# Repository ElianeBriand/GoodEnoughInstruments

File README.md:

PCB designs &amp; software for DIY instrumentation and random stuffs.

No guarantee whatsoever of fitness for purpose.

# Description of projects

- USB_JTAG: a 3.3v USB-to-JTAG board based on a FTDI chip. Can also be used in USB-to-Serial and other FTDI-supported mode. Finished and working

- Watercooling4cats: Formally a miniature air/floor cooler for my cat (gets hot in the summer). Based on watercooling supplies, a stock CPU fan and a peltier. Can be used as the cooling system for a thermally controlled small enclosure (with temperature feedback) when the cat considers it unnecessary. Hardware is mostly done (a few bodge to be added to the current board file), firmware being written (FreeRTOS-based)

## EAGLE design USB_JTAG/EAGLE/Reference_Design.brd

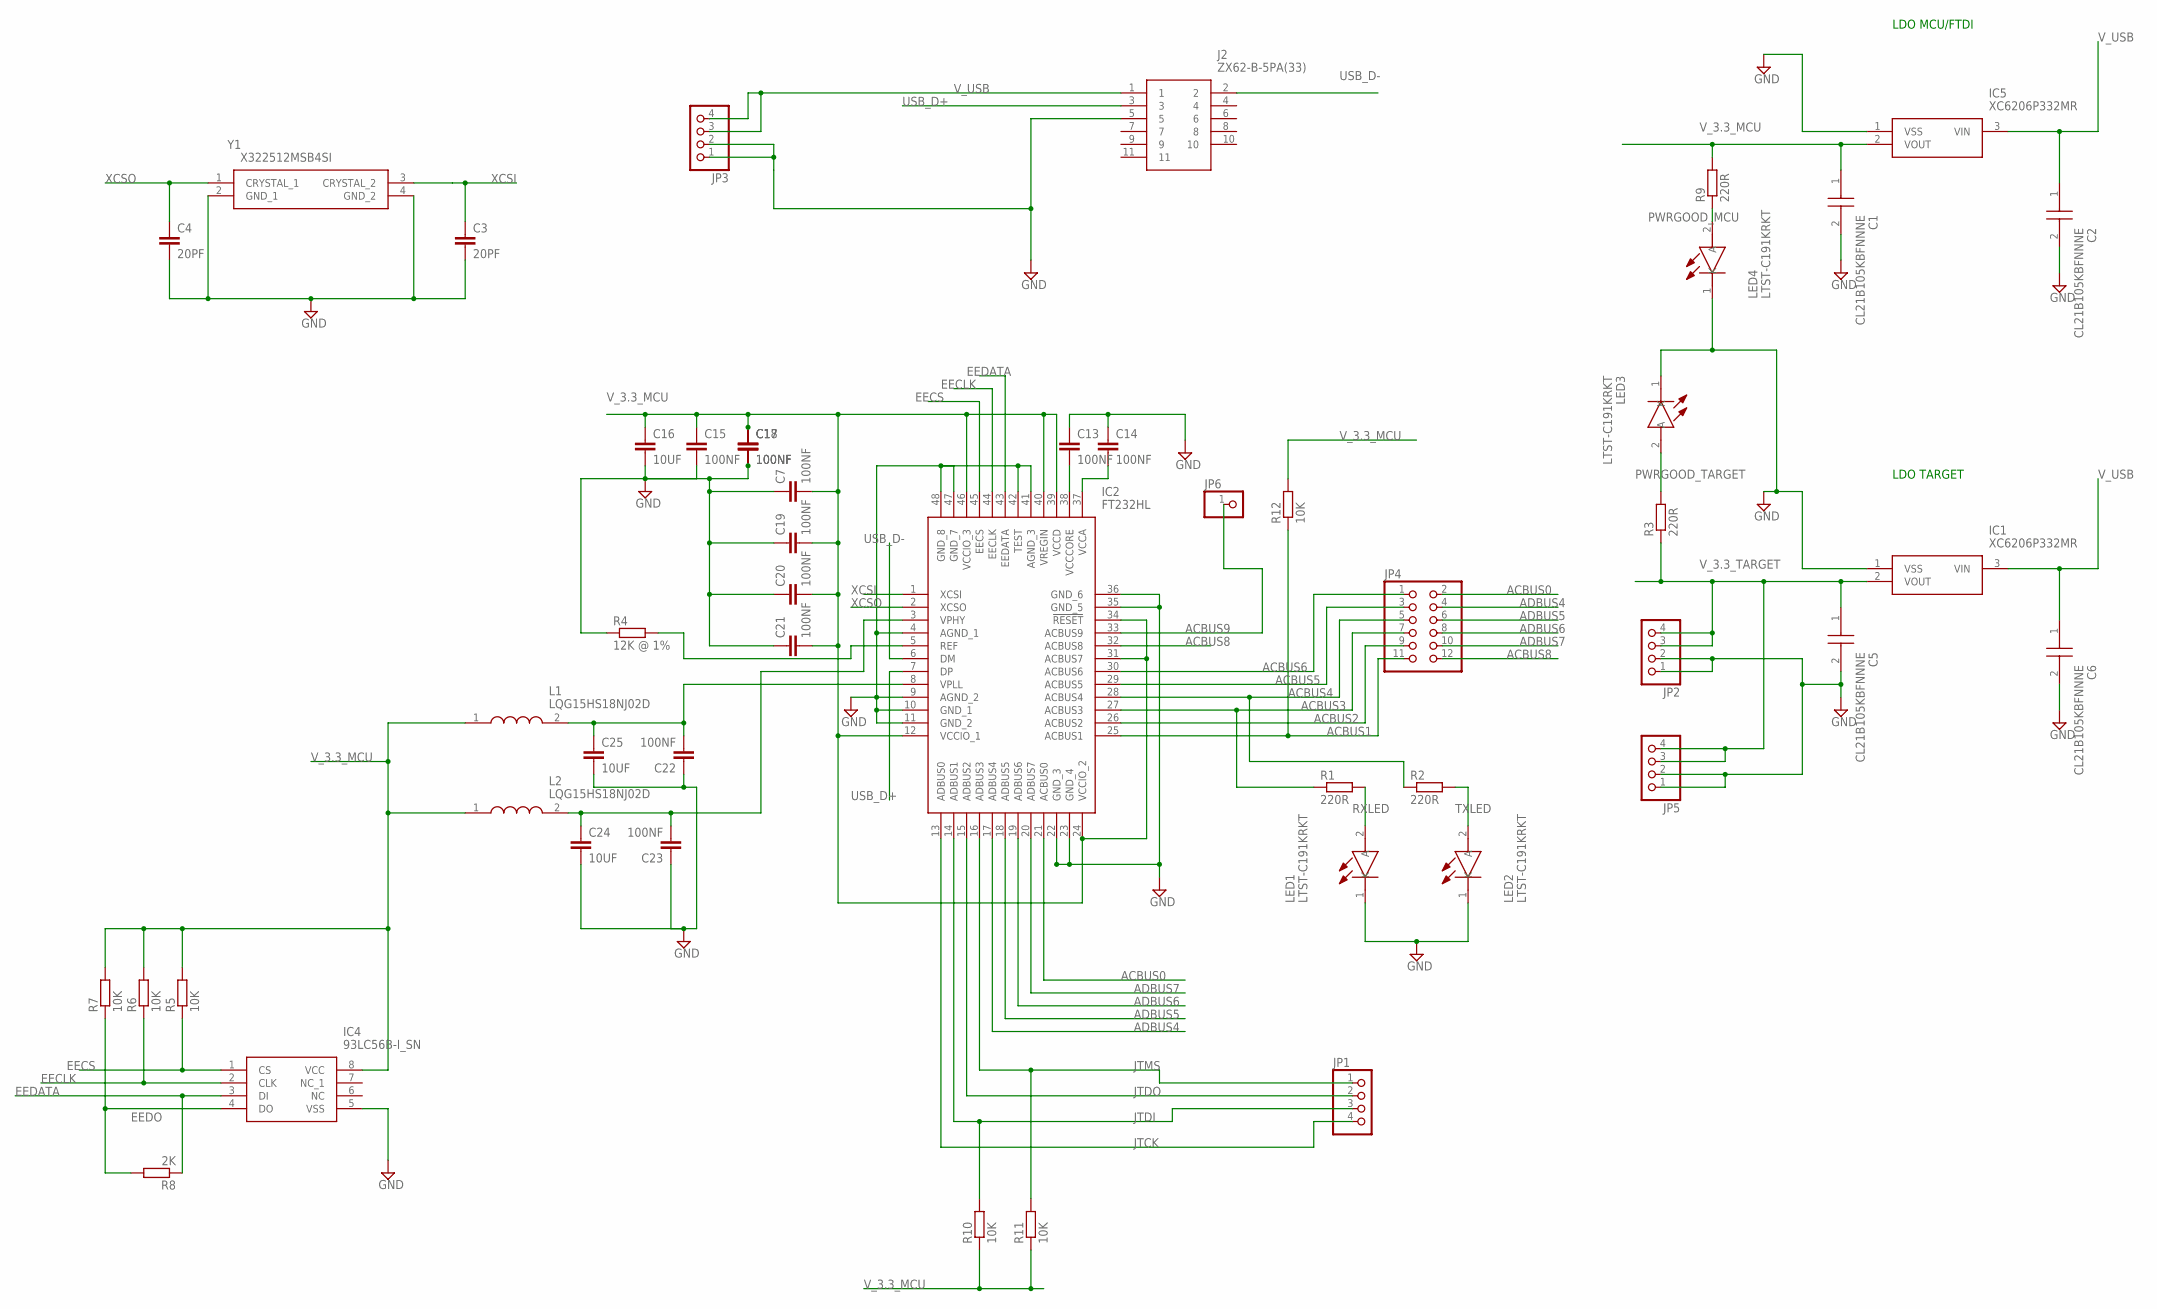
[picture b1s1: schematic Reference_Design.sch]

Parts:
C1, C2, C5, C6: CL21B105KBFNNNE; CAPC2012X135N
C3, C4: 20PF; C0603
C7, C13, C14, C15, C17, C18, C19, C20, C21, C22, C23: 100NF; C0603
C16, C24, C25: 10UF; C1206
IC1, IC5: XC6206P332MR; SOT95P280X130-3N
IC2: FT232HL; QFP50P900X900X160-48N
IC4: 93LC56B-I_SN; SOIC127P600X175-8N
J2: ZX62-B-5PA(33); ZX62B5PA33
JP1, JP2, JP3, JP5: PINHD-1X4; 1X04
JP4: PINHD-2X6; 2X06
JP6: PINHD-1X1; 1X01
L1, L2: LQG15HS18NJ02D; INDC1005X55N
LED1, LED2, LED3, LED4: LTST-C191KRKT; LEDC1608X55N
R1, R2, R3, R9: 220R; R0603
R4: 12K @ 1%; R0603
R5, R6, R7, R10, R11, R12: 10K; R1206
R8: 2K; R1206
Y1: X322512MSB4SI

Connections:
ACBUS0: IC2.21 (ACBUS0), JP4.2
ACBUS1: IC2.25 (ACBUS1), JP4.11, R12.1
ACBUS2: IC2.26 (ACBUS2), JP4.9
ACBUS3: IC2.27 (ACBUS3), JP4.7, R1.1
ACBUS4: IC2.28 (ACBUS4), JP4.5, R2.1
ACBUS5: IC2.29 (ACBUS5), JP4.3
ACBUS6: IC2.30 (ACBUS6), JP4.1
ACBUS8: IC2.32 (ACBUS8), JP4.12
ACBUS9: IC2.33 (ACBUS9), JP6.1
ADBUS4: IC2.17 (ADBUS4), JP4.4
ADBUS5: IC2.18 (ADBUS5), JP4.6
ADBUS6: IC2.19 (ADBUS6), JP4.8
ADBUS7: IC2.20 (ADBUS7), JP4.10
EECLK: IC2.44 (EECLK), IC4.2 (CLK), R6.1
EECS: IC2.45 (EECS), IC4.1 (CS), R5.1
EEDATA: IC2.43 (EEDATA), IC4.3 (DI), R8.1
EEDO: IC4.4 (DO), R7.1, R8.2
GND: C1.2, C2.2, C3.2, C4.2, C5.2, C6.2, C7.1, C13.1, C14.1, C15.2, C16.2, C17.2, C18.2, C19.1, C20.1, C21.1, C22.1, C23.1, C24.2, C25.2, IC1.1 (VSS), IC2.4 (AGND_1), IC2.9 (AGND_2), IC2.10 (GND_1), IC2.11 (GND_2), IC2.22 (GND_3), IC2.23 (GND_4), IC2.35 (GND_5), IC2.36 (GND_6), IC2.41 (AGND_3), IC2.42 (TEST), IC2.47 (GND_7), IC2.48 (GND_8), IC4.5 (VSS), IC5.1 (VSS), J2.5, JP2.1, JP2.2, JP3.1, JP3.2, JP5.1, JP5.2, LED1.1 (K), LED2.1 (K), LED3.1 (K), LED4.1 (K), R4.1, Y1.2 (GND_1), Y1.4 (GND_2)
JTCK: IC2.13 (ADBUS0), JP1.4
JTDI: IC2.14 (ADBUS1), JP1.3, R10.2
JTDO: IC2.15 (ADBUS2), JP1.2
JTMS: IC2.16 (ADBUS3), JP1.1, R11.2
PWRGOOD_MCU: LED4.2 (A), R9.1
PWRGOOD_TARGET: LED3.2 (A), R3.2
REF: IC2.5 (REF), R4.2
RXLED: LED1.2 (A), R1.2
TXLED: LED2.2 (A), R2.2
USB_D+: IC2.7 (DP), J2.3
USB_D-: IC2.6 (DM), J2.2
VCCA: C14.2, IC2.37 (VCCA)
VCCCORE: C13.2, IC2.38 (VCCCORE)
VPHY: C23.2, C24.1, IC2.3 (VPHY), L2.2
VPLL: C22.2, C25.1, IC2.8 (VPLL), L1.2
V_3.3_MCU: C1.1, C7.2, C15.1, C16.1, C17.1, C18.1, C19.2, C20.2, C21.2, IC2.12 (VCCIO_1), IC2.24 (VCCIO_2), IC2.31 (ACBUS7), IC2.34 (!RESET), IC2.39 (VCCD), IC2.40 (VREGIN), IC2.46 (VCCIO_3), IC4.8 (VCC), IC5.2 (VOUT), L1.1, L2.1, R5.2, R6.2, R7.2, R9.2, R10.1, R11.1, R12.2
V_3.3_TARGET: C5.1, IC1.2 (VOUT), JP2.3, JP2.4, JP5.3, JP5.4, R3.1
V_USB: C2.1, C6.1, IC1.3 (VIN), IC5.3 (VIN), J2.1, JP3.3, JP3.4
XCSI: C3.1, IC2.1 (XCSI), Y1.3 (CRYSTAL_2)
XCSO: C4.1, IC2.2 (XCSO), Y1.1 (CRYSTAL_1)

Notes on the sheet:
LDO MCU/FTDI
LDO TARGET

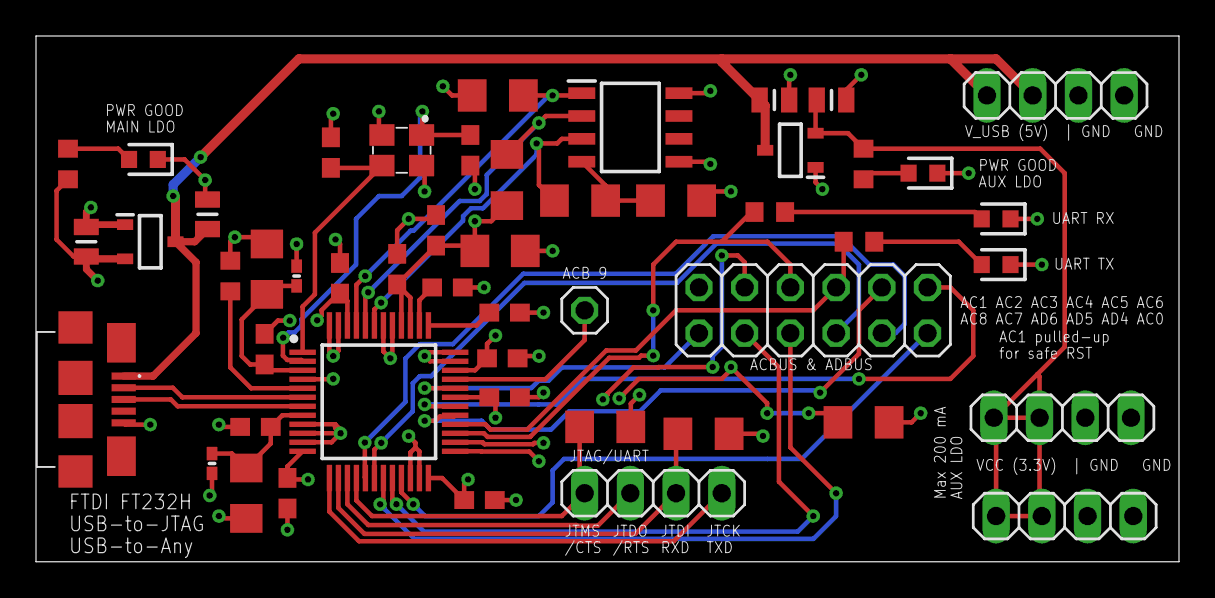
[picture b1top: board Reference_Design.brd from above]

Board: 4 copper layers, 63.5 x 29.2 mm, 50 parts (0 on the bottom side), 38 nets.

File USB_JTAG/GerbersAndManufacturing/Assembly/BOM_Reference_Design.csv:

"Qty";"Value";"Device";"Package";"Parts";"Description";"ALLIED_NUMBER";"ALLIED_PRICE-STOCK";"DESCRIPTION";"HEIGHT";"MANUFACTURER_NAME";"MANUFACTURER_PART_NUMBER";"MOUSER_PART_NUMBER";"MOUSER_PRICE-STOCK";"POPULARITY";"RS_PART_NUMBER";"RS_PRICE-STOCK";"SPICEPREFIX";
"1";"";"PINHD-1X1";"1X01";"JP6";"PIN HEADER";"";"";"";"";"";"";"";"";"64";"";"";"";
"4";"";"PINHD-1X4";"1X04";"JP1, JP2, JP3, JP5";"PIN HEADER";"";"";"";"";"";"";"";"";"91";"";"";"";
"1";"";"PINHD-2X6";"2X06";"JP4";"PIN HEADER";"";"";"";"";"";"";"";"";"8";"";"";"";
"11";"100NF";"C-EUC0603";"C0603";"C7, C13, C14, C15, C17, C18, C19, C20, C21, C22, C23";"CAPACITOR, European symbol";"";"";"";"";"";"";"";"";"73";"";"";"C";
"6";"10K";"R-EU_R1206";"R1206";"R5, R6, R7, R10, R11, R12";"RESISTOR, European symbol";"";"";"";"";"";"";"";"";"41";"";"";"R";
"3";"10UF";"C-EUC1206";"C1206";"C16, C24, C25";"CAPACITOR, European symbol";"";"";"";"";"";"";"";"";"54";"";"";"C";
"1";"12K @ 1%";"R-EU_R0603";"R0603";"R4";"RESISTOR, European symbol";"";"";"";"";"";"";"";"";"70";"";"";"R";
"2";"20PF";"C-EUC0603";"C0603";"C3, C4";"CAPACITOR, European symbol";"";"";"";"";"";"";"";"";"73";"";"";"C";
"4";"220R";"R-EU_R0603";"R0603";"R1, R2, R3, R9";"RESISTOR, European symbol";"";"";"";"";"";"";"";"";"70";"";"";"R";
"1";"2K";"R-EU_R1206";"R1206";"R8";"RESISTOR, European symbol";"";"";"";"";"";"";"";"";"41";"";"";"R";
"1";"93LC56B-I_SN";"93LC56B-I_SN";"SOIC127P600X175-8N";"IC4";"2K,128 X 16,Serial EE,SOIC-8";"70045309";"http://www.alliedelec.com/microchip-technology-inc-93lc56b-i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";"2K,128 X 16,Serial EE,SOIC-8";"1.75mm";"Microchip";"93LC56B-I/SN";"579-93LC56BISN";"https://www.mouser.com/Search/Refine.aspx?Keyword=579-93LC56BISN";"";"0454347P";"http://uk.rs-online.com/web/p/products/0454347P";"";
"4";"CL21B105KBFNNNE";"CL21B105KBFNNNE";"CAPC2012X135N";"C1, C2, C5, C6";"SAMSUNG ELECTRO-MECHANICS - CL21B105KBFNNNE - CERAMIC MULTILAYER MLCC CAPACITORS- SMD";"";"";"SAMSUNG ELECTRO-MECHANICS - CL21B105KBFNNNE - CERAMIC MULTILAYER MLCC CAPACITORS- SMD";"1.35mm";"Samsung Electro-Mechanics";"CL21B105KBFNNNE";"N/A";"https://www.mouser.com/Search/Refine.aspx?Keyword=N%2FA";"";"";"";"";
"1";"FT232HL";"FT232HL-REEL";"QFP50P900X900X160-48N";"IC2";"USB 2.0 to UART/FIFO Interface, LQFP48 FTDI Chip FT232HL-REEL Universal Asynchronous Receiver & Transmitter RS232, RS422, RS485 UART 12Mbit/s, 1.8 V, 3.3 V";"70069390";"http://www.alliedelec.com/ftdi-ft232hl-reel/70069390/";"USB 2.0 to UART/FIFO Interface, LQFP48 FTDI Chip FT232HL-REEL Universal Asynchronous Receiver & Transmitter RS232, RS422, RS485 UART 12Mbit/s, 1.8 V, 3.3 V";"1.6mm";"FTDI Chip";"FT232HL-REEL";"895-FT232HL-REEL";"https://www.mouser.com/Search/Refine.aspx?Keyword=895-FT232HL-REEL";"";"7377843P";"http://uk.rs-online.com/web/p/products/7377843P";"";
"2";"LQG15HS18NJ02D";"LQG15HS18NJ02D";"INDC1005X55N";"L1, L2";"Murata LQQ15HN Series Wire-wound SMD Inductor 0.018 uH +/-5% 300mA Idc Q:8";"";"";"Murata LQQ15HN Series Wire-wound SMD Inductor 0.018 uH +/-5% 300mA Idc Q:8";"0.55mm";"Murata Electronics";"LQG15HS18NJ02D";"81-LQG15HS18NJ02D";"https://www.mouser.com/Search/Refine.aspx?Keyword=81-LQG15HS18NJ02D";"";"7254910";"https://uk.rs-online.com/web/p/products/7254910";"";
"4";"LTST-C191KRKT";"LTST-C191KRKT";"LEDC1608X55N";"LED1, LED2, LED3, LED4";"Standard LEDs - SMD Red Clear 631nm";"";"";"Standard LEDs - SMD Red Clear 631nm";"0.55mm";"Lite-On";"LTST-C191KRKT";"859-LTST-C191KRKT";"https://www.mouser.com/Search/Refine.aspx?Keyword=859-LTST-C191KRKT";"";"1278415P";"http://uk.rs-online.com/web/p/products/1278415P";"";
"1";"X322512MSB4SI";"X322512MSB4SI";"X322512MSB4SI";"Y1";"SMD Crystal Resonators 12MHz +/-10ppm SMD-3225_4P RoHS";"";"";"SMD Crystal Resonators 12MHz +/-10ppm SMD-3225_4P RoHS";"0.8mm";"Yangxing Tech";"X322512MSB4SI";"";"";"";"";"";"";
"2";"XC6206P332MR";"XC6206P332MR";"SOT95P280X130-3N";"IC1, IC5";"Low ESR Cap.Compatible Postive Voltage Regulators";"";"";"Low ESR Cap.Compatible Postive Voltage Regulators";"1.3mm";"Torex";"XC6206P332MR";"";"";"";"";"";"";
"1";"ZX62-B-5PA(33)";"ZX62-B-5PA(33)";"ZX62B5PA33";"J2";"USB Connectors MICRO B RECEPT RA SMT BTTM MNT";"";"";"USB Connectors MICRO B RECEPT RA SMT BTTM MNT";"2.8mm";"Hirose";"ZX62-B-5PA(33)";"798-ZX62-B-5PA33";"https://www.mouser.com/Search/Refine.aspx?Keyword=798-ZX62-B-5PA33";"";"1362267";"http://uk.rs-online.com/web/p/products/1362267";"";

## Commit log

2019-11-09 USB JTAG
2019-12-23 USB-JTAG board picture
2020-09-04 Added Watercooling4cat project
